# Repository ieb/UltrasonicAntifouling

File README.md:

# Ultrasonic Antifouling Mk2.

My Mk1 unit finally failed after 4 years contnuous permanently on. It was only restarted when there were powercuts on shorepower. If failed because of salt getting onto the back of the board causing a short which blew the Arduino. Rather than fix, I decided to build Mk2. This time its taken 2 weeks of evenings. Last time two months.

The design is much simpler. It uses the PWM output of the Atmel328p Timer1 running off a 16MHz 5V pro mini with no pre-scaler. The MOSFET drivers are still used over driving the MOSFETs from logic levels, but there is not precise frequency generator the variable power is simplified to run in 3 states depending on input voltage. Anything over 13.7 runs at high power consumption. 13.7 to 12 at half power consumption. Below 12 the 328p goes into a sleep mode drawing 20mA until the supply voltage returns. 

This time, rather than driving 6 channels from a single Ardiono I am dedicating an Ardiono Pro Mini to each channel, and putting each in their own IP67 sealed box, with a thermally coupled external heatsink. This eliminates 600V high frequency being routed round the boat, which never felt right.

# Variable Frequency Ultrasound generator

This code generated 2 complementary square waves to drive MOSFETS to produce untrasound output. It will operate from about 200Hz to 250KHz with PWM 0-100% and deadtime control in microseconds.

It uses that standard Arduino PWM output, using the 16 bit timer 1 in mode 8 (see http://ww1.microchip.com/downloads/en/DeviceDoc/en590320.pdf) which is Phase Correct, frequency correct. The prescalar is set to 1 so the counter operates at 16MHz (Uno 5v, 16MHz). The counter counts up from 0 to the TOP value (in register ICR1) and down to zero again. 

Setup of the PWM is controlled by the registers

        TCCR1A = (TCCR1A & 0x0F) | 0xB0 ; // set pin 10 inverted  and pin 9 normal ie 0b1011xxxx
        TCCR1A = (TCCR1A & 0xFC) | 0x00 ; // phase correct pwm, mode 8, ie 0bxxxxxx00
        TCCR1B = (TCCR1B & 0xE7) | 0x10 ; // phase correct pwm, mode 8, ie 0bxxx10xxx

        TCCR1B = (TCCR1B & 0x0F8) | 0x01 ; // full speed 16MHz clock 0bxxxx001 = 16MHz 

Frequency = 16MHz/1/(2*ICR1) since the counter has to count up and down for each period of output. 

The tigger value of channel A (pin 9) is set to set digital to low at greater than a threashold value and the trigger value of channel B (pin 10) is set to set digital low below a value. As the counter ramps up channel B is turned off and after the dead time ticks have passed challen A is turned on.  Deadtime is equally spaced arround the TOP/2.  

The levels can be calculated as follows

        uint16_t deadTimeTicks = deadTimeMicros*8; // 16MHz clock, deadTimeTicks is from center so /2

        uint16_t counterTopValue = (uint16_t)(16000.0/(2*frequencyKhz));

        uint16_t center = counterTopValue/2;
        OCR1A = counterTopValue-((center-deadTimeTicks)*percent)/100;
        OCR1B = ((center-deadTimeTicks)*percent)/100;

The output needs to be fed into an inverting mosfet driver drivng a pair of mosfets driving a center tapped coil with all the normal protections. Deadtime need to be calculated based on the inductance of the coil to ensure the mostfets switch off correctly between pulses.

One anomaly that was discovered in testing, if the timer is left to run every now and again when it wraps round a super long pulse is output. This can result in not enough deadtime at which point both MOSFETS will latch up, and if there isnt a current limiting device blow them or the fuse. I used a 21w 12v bulb during testing which would light up when there was an over current event.

The fix is to zero the TCNT1 register before each pulse of output ensuring no wrap round occurs.

# Output screenshots

These are for a inverting driver, see Ultrasound.begin() for details on how to generate non invertig output.

# Driver and code

The driver is derived from the Jaycar circuit which uses a 5V PIC to drive the IRF540N mosfets directly. Instead this uses a RFP50N06 and a MCP14E4 dual 4.5A Mosfet driver capable of driving the gate(2200pf) of the Mosfet in about 15ns using guidance from Microchip design notes. Ramp on scopes confirms this. I found IRF540Ns are not robust enough to be driven with a clean 12v square wave. Output is upto 700v peak to peak. I get minimal ringing in the mosfet drive or the mosfet output with this setup and the high voltage output even looks like a clean sie wave at some frequencies.

Running the Arduino connected to a computer over serial port is not advised with the output enabled.

# Sequence

I found with the previous 6 chanel versiom that although I had an elaborate configurtion method over serial, I never used it, and connecting a usb port to this board without proper isolation potentially exposes the computer to 600V or more if something goes wrong. So I hard code the sequence and flash the pro mini to make change with the power side of the driver disabled.

In The version 2 software I had a complex output going upto 100KHz, but research indicats that while algae are discupted above 40KHz it requires very high power levels (60W or more). The researc reports that hard fouling is impacted most in the 20-30KHz range.

So this version changes the 40KHz transducers with larger 27KHz transducers and outputs between 20 and 40Khz in 100Hz steps for 600ms At full power there is a 1.4 pause between frequencies. In low power this extends to 2.4s with an extended pause every 20 steps.

Monitoring on a scope indicates the output of the 27Khz transducer is upto 30W at peak power in areas of resonance.

# LEDS

The onboard led flashes to indicate state.  Flash period is 200ms. This approach seems complex but anyone who has been at sea at night might enjoy the port hand marker impression. The reason for the flashes are to help diagnose the units behaviour without having to get a volt meter out. Couloured leds might have been easier to understand.

On boot the battery state and any fault status is reported. The fault must be fixed before the unit will power up, on boot. After boot the unit will continue to function but will report the fault on every cycle.

* Slow on off. - Normal operation state changes each time the ultrasound is switched on.
* 2 flasses power supply > 13.6v, ultrasound will operate at lower power consumption.
* 3 flasses power supply > 12.0v, ultrasound off
* 4 flashes means supply voltage is too high > 15v, the unit will not run
* 5 flashes means the initial slow charge failed to reach > 10.5v
* 6 flashes means the charge failed to sabalise at less than 2V below the supply voltage, probably a failed mosfet.
* 7 flashes means supply is turned off.
* 8 flashes means supply is on but too low to start loadswitch.
* 10 flashes means supply is turned off due to overtemp

During operation the led occults (off-on-off) as the frequency changes. At the end of each set of frequencies, voltages are checked and the unit may goin into one of 3 states.

* Standby due to a supply voltage < 12.0v, 3 flashes followed by a 60s sleep, folled by a check which may report 4 to 7 flashes.
* Low power, voltage < 13.7, 2 flashes every 5s for 30s followed by a check which may report 4 to 7 flashes.
* Full power, no flashes just a 5s sleep between operations.

# Output.

Output comes out at 757v peak to peak at masimum dropping off a bit at higher frequencies. The output wave is a lot cleaner and more sinusoidal than before, and the output sequence seems to generate more ultrasound for longer than before.

# Prototype

The prototype is on a double sided CNC milled PCB, which has been thourugly hacked to get the board quiet and efficient with minimal interference on supply line. Following units will have less hacked boards, and probably more surface mount components.

# Initial testing

Initial testing installing the driver onboard driven by a 10A switch mode power supply indicated that the surge current charging the main capacitor was well over 26A. Attempts to get the capacitor charged to start the device blew the 10A fuse and caused the power supply to shutdown due to overcurrent. So, we need a soft start mechanism. The super simple, safe, but ugly quickfix was to replace the fuse with a 21W 12V lightbulb, neatly limiting the inrush current to 2A and providing a quick over current shutdown. Its also a great indicator to show when the device is drawing more than 1A as it glows or lights up. Lifetime is probably limited. So a better solution is needed.

# Soft start and/or current limit.

Provided the device is operating correct, and the code is written to not exercise frequencies that draw excessive current for too long (eg 60KHz for the same period as 20KHz requires more energy), then a current limit is not required, only Soft start with the ability to shut down.

# Load switches

Load switches are generally P-Channel Mosfets or N-Channel. P Channel are more expensive, have higher resistence for the same die size. The aim is to turn the mosfet on slowly to reduce the current inrush, but once on keep the mostef saturated so it doesnt dissapate power and hence heat. 

# P-Channel Load switch.

This is relatively simple. Charge a capacitor between gate and source charged by the supply voltage, with a time constant that ensures the gate voltage ramps down (Vgs(th) is -ve) at a rate that ballances current against switch on time to limit the mosfet heat up. It needs a few components and an extra nmos transistor to turn the switch on. The turn on signal comes from a gio pin going high, turn off when its taken low. Model in ltspice/pchannel-softstart.asc.  Power dissapation when fully switched on is about double for a comparable P channel, and about 0.5w. This may need to he taken into account.

# N-Channel Load Switch

This is harder. The gate needs to be above the threshold voltage of the source, which when fully turned will be the same as the drain (supply voltage), so the gate needs to be at a higher voltage than the supply voltage. The solution is to use a charge pump, pumped by a square wave from the Arduino PWM output (50/50), assumning there is a spare. The copmbination of frequency of PWM, pump capacitor value and storage capacitor value controls the ultimate voltage achieved by the charge pump which tends towards the voltage of pwm output. Because the pump is decoupled from ground and coupled to the source, the voltage at the gate can rise above the absolute voltage of the suppy, and hence go fully on. Increasing the pwm frequency increases the slope, inrush current and peak power during turn on. The component count is less, and the components are less expensive, but it requires active MCU control to run.  Model in ltspice/nchannel-softstart.asc

# Filtering

Although the current driver doesnt appear to generated high frequency interference into the supply line, some sort of low pass filter should be added. LTSpice (ltspice/filter.asc) simulations indicate a 330uH coil will result in a 30mV ripple in the supply line at 1KHz, and a lot less at higher frequencies. The p-channel load switch is completely immune to the impact of a ripple, but the charge pump in the n-channel load switch is disrupted by any ripple to the extent that if it is large enough the mosfet will turn on and off and disapate more than 10W. Additionally, the mosfet remains on for as long as the ripple is present regardless of whatever the pwm is doing. Hence for the n-channel load switch a low pass filter is required to reduce the influence of any ripples generated by the driver on its operaiton. For a p-channel switch a low pass LC filter is desirable just in case any transients disrupt the mosfet or make it back to the supply line.

The v2 board generates a 4MHz ripple after that mosfets turn on that decays after 3 cycles. This is probably due to excessive paracitic capacitance in the primary coil of the transformer. Reducing the ramp rate to the gate makes little difference and attempts at altering the fequency by adding capacitance only increase heat and power consumption as a result of resonance at lower fequencies. Still looking for a solution to eliminate this resonance.

# Soft start control

The control depends on the type of switch being used. For P-Channel it can be simple digital IO pin. For the n-channel it needs to be a PWM signal at between 1KHz and 20KHz depending on the R and C values chosen in the charge pump. Standard Arduino PWM runs at 490Hz so the same techniques as with the driver will be needed. The duty cycle of the PWM can be fixed which gives a little more flexibility with which timer can be used. 

Timer1 is used for the ultrasound. Since the power enable needs to be running continuously Timer 1 cannot be re-used for this purpose. 
Timer 0 is 8bit PWM mapped to pins 5 and 6 but is used internally for millis() and delay() so the pre-scaler cannot be changed without impacting those functions.
Timer 2 is an 8bit timer on pins 11 (A) and 3(B)
Documentation page 150 in http://ww1.microchip.com/downloads/en/DeviceDoc/en590320.pdf
Fast PWM  mode goes between 0 and 0xff so only has relatively fixed frequencies
16000/(N*256), where N is 1,8,32,64,256,1024 ie 62.5,7.8,1.9,0.97,0.244,0.061 KHz
Since we need 50% PWM, standard mode may be better with the frequency changed using OCR0 register.

16000/(2*N*(1+OCRn))
N=64 gives 125 -> 0.490 KHz 
OCRn=10 = 10.4KHz
OCRn=20 = 5.9KHz
OCRn=40 = 3.8KHz
OCRn=80 = 1.5KHz
OCRn=80 = 1.5KHz
OCRn=160 = 0.7KHz
etc

# Soft start testing

Using a frequency of 5KHz for start and 40KHz for on workd, however the IRF540 Vgs at 4.5v is too low to turn the Mosfet fully on. Switching to a IRL540 (logic level), with 0.5KHz start and 20KHz on works perfectly. The inrush current is down from 26A to 0.5A and so far the IRL540 is remaining cool. 0.5Khz generates a Vgs of about 1.4v. 20KHz is about 4.5v.

# Peak current.

At resonance and frequencies above 60Khz the current rises above the current limit on the bench supply, so there will need to be some adjustment to the energy pushed into the transducer at the top end of the range so that 3x transduces dont overload a 10A switch mode supply causing it to trip.

# Heat

Looking at the v2 board with a FLIR device showed that the MCP14E4 was overheating drawing 100mA due to a fault, normally 1mA at reset. The device was broken in some way and replaced. Once fixed the unit was run for 30 after which time the board was checked again. All components were < 25C except for the core of the coil which was at 40C, it probably needs to be connected via an aluminium strip to the heatskink, and there needs to be a thermistor so the Arduino can shutdown in the event the temperature rises too high. MFR52-10K NTC will measure 4.354K at 45C see https://www.gotronic.fr/pj2-mf52type-1554.pdf. Pathching the v2 board with a simular NCT works acceptably.

# Transformer

The output of the device is about 600v peak to peak which is probably too high for the transducers and will cause premature failure. I reused transformers from the preveous generator. Unwinding the coils refealed a 4-0-4 primary and a 0-90 secondary. Since the primary is driven alternately the effective peak to peak is 28v on a 14v supply making the peak to peak output 630v which is too high and is the reason the pulse pattern needed to be so short.

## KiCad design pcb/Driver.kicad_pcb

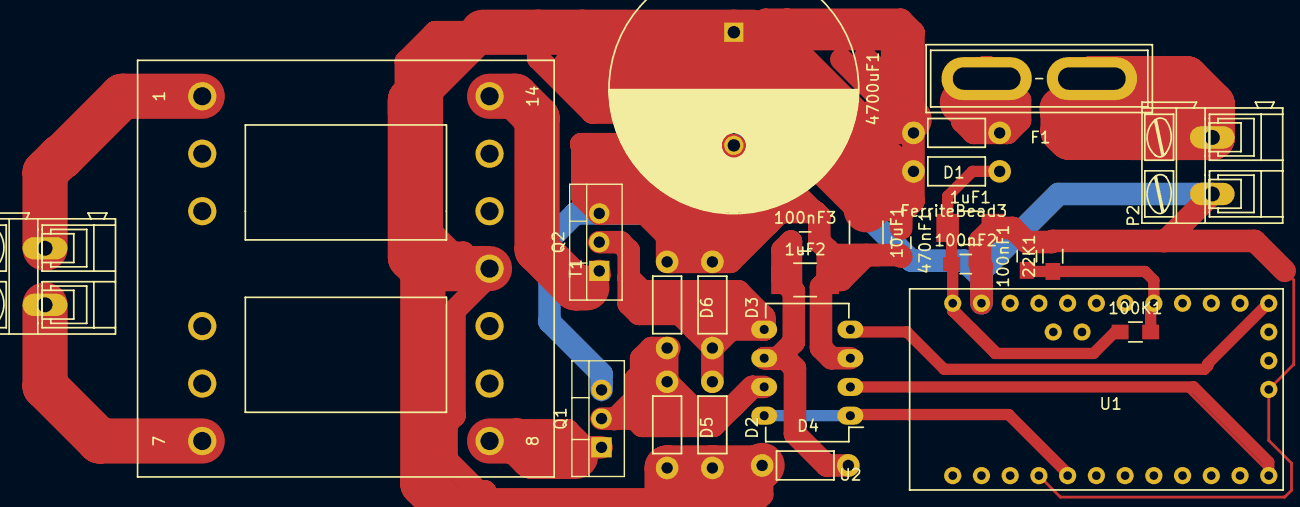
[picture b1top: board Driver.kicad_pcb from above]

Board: 2 copper layers, 25 parts (0 on the bottom side), 16 nets.

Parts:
1uF1, 1uF2, 10uF1: CAPAPOL; C_1210_HandSoldering
22K1, 100K1: R; R_0805_HandSoldering
100nF1, 100nF2, 100nF3, 470nF1: C; C_0805_HandSoldering
4700uF1: CAPAPOL; C_Radial_D22_L41_P10
D1, D2, D3, D4, D5, D6: 1N5819; Resistor_Horizontal_RM7mm
F1: FUSE; BladeFuse-CarType
FerriteBead3: INDUCTOR; Resistor_Horizontal_RM7mm
P1, P2: CONN_2; AK300-2
Q1, Q2: IRF540N; TO-220_Vertical
T1: ETD29; ETD29_13Pin_Horizontal_EPCOS-B66359A1013T
U1: ArdinoMinPro; ArduinoProMini
U2: MCP14E3; DIP-8_W7.62mm_LongPads

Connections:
12v: 1uF1.1, 100K1.1, 100nF2.1, FerriteBead3.1, U1.24
12vPower: 10uF1.1, 470nF1.1, 4700uF1.1, D1.2, D2.2, D4.1, D5.2, FerriteBead3.2, T1.11
ADC1: 22K1.1, 100K1.2, 100nF1.1, U1.17
ENPWM: U1.5, U2.1, U2.8
GND: 1uF1.2, 1uF2.2, 10uF1.2, 22K1.2, 100nF1.2, 100nF2.2, 100nF3.2, 470nF1.2, 4700uF1.2, D3.1, D6.1, P2.1, Q1.3, Q2.3, U1.4, U1.23, U1.31, U2.3
unnamed: 1uF2.1, 100nF3.1, D4.2, U2.6
unnamed: D1.1, F1.2
unnamed: D2.1, D3.2, Q2.2, U2.5
unnamed: D5.1, D6.2, Q1.2, U2.7
unnamed: F1.1, P2.2
unnamed: P1.1, T1.7
unnamed: P1.2, T1.1
unnamed: Q1.1, T1.8
unnamed: Q2.1, T1.14
PWMA: U1.12, U2.2
PWMB: U1.13, U2.4

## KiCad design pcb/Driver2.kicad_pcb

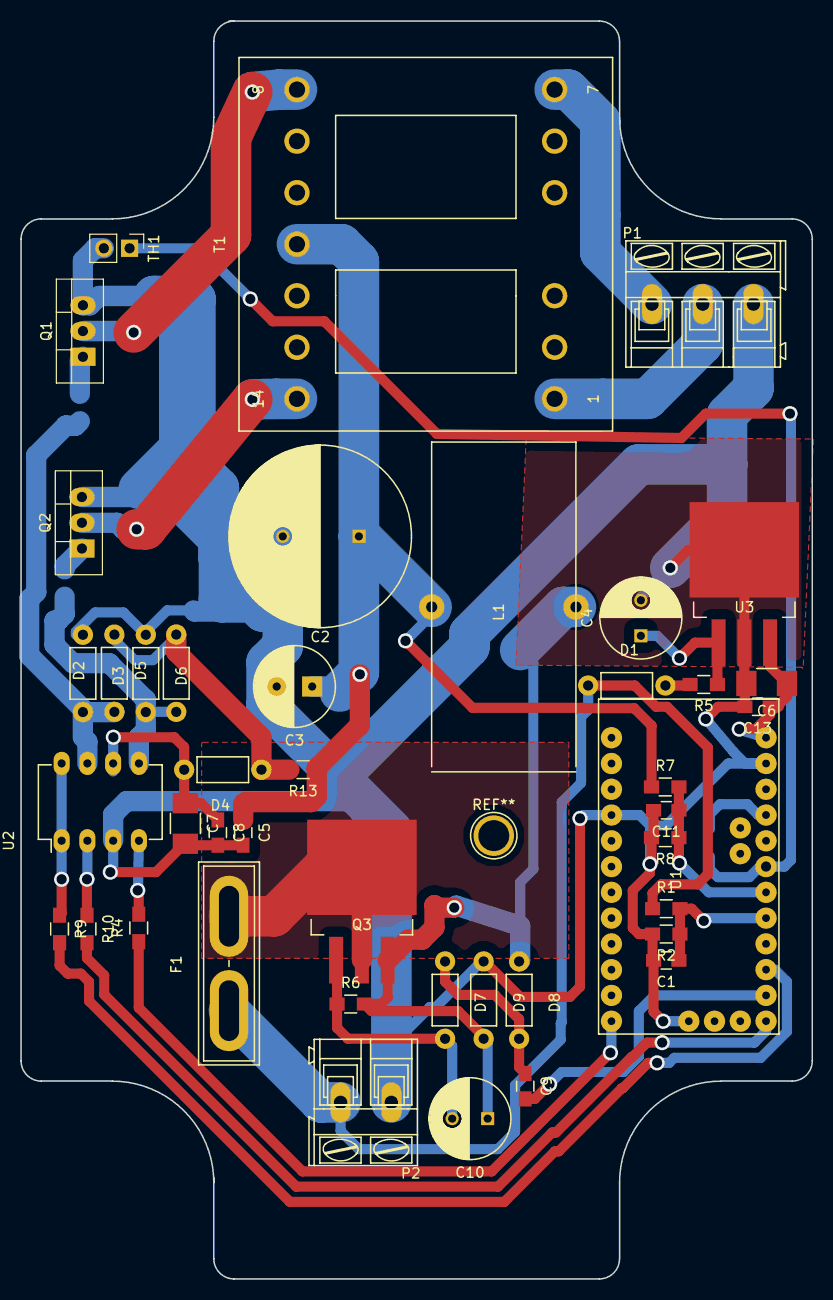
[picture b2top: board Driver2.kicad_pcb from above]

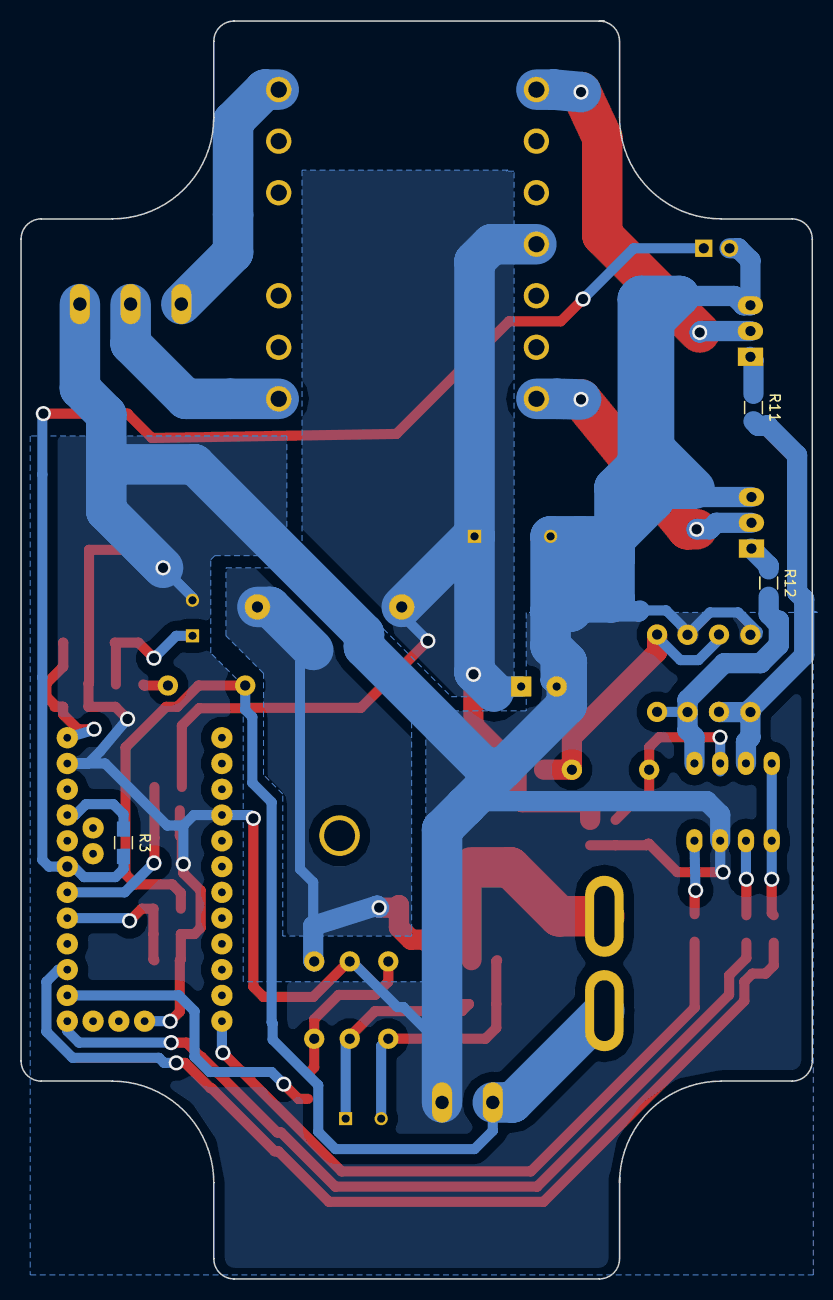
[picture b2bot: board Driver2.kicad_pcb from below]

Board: 2 copper layers, 78.0 x 124.0 mm, 46 parts (3 on the bottom side), 31 nets.

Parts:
C1, C8, C11, C13: 100nF; C_0805_HandSoldering
C2: 4700uF 50V; C_Radial_D18_L36_P7.5
C3: 330uF 50v; C_Radial_D8_L11.5_P3.5
C4: 100uF; C_Radial_D8_L11.5_P3.5
C5: 470nF; C_0805_HandSoldering
C6, C7: 1uF; C_1210_HandSoldering
C9: 10nF; C_0805_HandSoldering
C10: 10uF; C_Radial_D8_L11.5_P3.5
D1, D2, D3, D4, D5, D6, D7, D8, D9: 1N5819; Resistor_Horizontal_RM7mm
F1: FUSE; BladeFuse-CarType
L1: 330uH 5A TBC; Choke14x32
P1: CONN_2; AK300-3
P2: CONN_2; AK300-2
Q1, Q2: RPF60N06; TO-220_Vertical
Q3: IRL540; TO-263-3Lead
R1, R6, R7: 100K; R_0805_HandSoldering
R2, R8: 22K; R_0805_HandSoldering
R3: 10K; R_0805_HandSoldering
R4, R9, R10: 120R; R_0805_HandSoldering
R5: 22R; R_0805_HandSoldering
R11, R12, R13: 0R; R_0805_HandSoldering
T1: ETD29; ETD29_13Pin_Horizontal_EPCOS-B66359A1013T
TH1: MF52-103 Thermistor 10K; Pin_Header_Straight_1x02_Pitch2.54mm
U1: ArdinoMinPro; ArduinoProMini
U2: MCP14E4; DIP-8_W7.62mm_LongPads
U3: LM7808ACT; TO-263-3Lead

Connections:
5v: R3.1, U1.21
8v: C6.1, C13.1, U1.24, U3.3
12v: D1.1, F1.1, P2.2, R1.1
12vPower: C2.1, C3.1, C5.1, L1.2, R7.1, R13.1, T1.11
ADC1: C1.1, R1.2, R2.1, U1.17
ADC2: C11.1, R7.2, R8.1, U1.18
ADC3: R3.2, TH1.1, U1.19
ENPWM: R9.1, U2.1, U2.8
GND: C1.2, C2.2, C3.2, C4.2, C5.2, C6.2, C7.2, C8.2, C11.2, C13.2, D3.1, D6.1, D9.1, P1.3, P2.1, Q1.3, Q2.3, R2.2, R8.2, TH1.2, U1.4, U1.23, U1.31, U2.3, U3.2
unnamed: C4.1, R5.1, U3.1
unnamed: C7.1, C8.1, D4.2, U2.6
unnamed: C9.1, D7.1, D8.2
unnamed: C10.1, D8.1, D9.2, L1.1, Q3.3, R6.2
unnamed: C10.2, D7.2, Q3.1, R6.1
unnamed: D1.2, R5.2
unnamed: D2.1, D3.2, R11.2, U2.7
unnamed: D2.2, D4.1, D5.2, R13.2
unnamed: D5.1, D6.2, R12.2, U2.5
unnamed: F1.2, Q3.2
unnamed: P1.1, T1.7
unnamed: P1.2, T1.1
unnamed: Q1.1, R11.1
unnamed: Q1.2, T1.8
unnamed: Q2.1, R12.1
unnamed: Q2.2, T1.14
unnamed: R4.1, U1.12
unnamed: R9.2, U1.15
unnamed: R10.2, U1.13
PWMA: R10.1, U2.2
PWMB: R4.2, U2.4
PWRENABLE: C9.2, U1.14

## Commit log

2021-04-22 Initial commit, working code
2021-04-25 moved to non inverting drives due to shortages of MCP14E3
2021-05-02 Rev 1 working code, schematic updated, pcb todo
2021-05-02 Writeup
2021-05-07 Added loadswitch to avoid inrush
2021-05-12 Working version with soft start, some frequency adjustments to come
2021-05-12 Updated documentation
2021-05-15 v2 board complete with temperature sensor on power components
2022-10-24 v3, targetting 20-30KHz with 27KHz transducers
